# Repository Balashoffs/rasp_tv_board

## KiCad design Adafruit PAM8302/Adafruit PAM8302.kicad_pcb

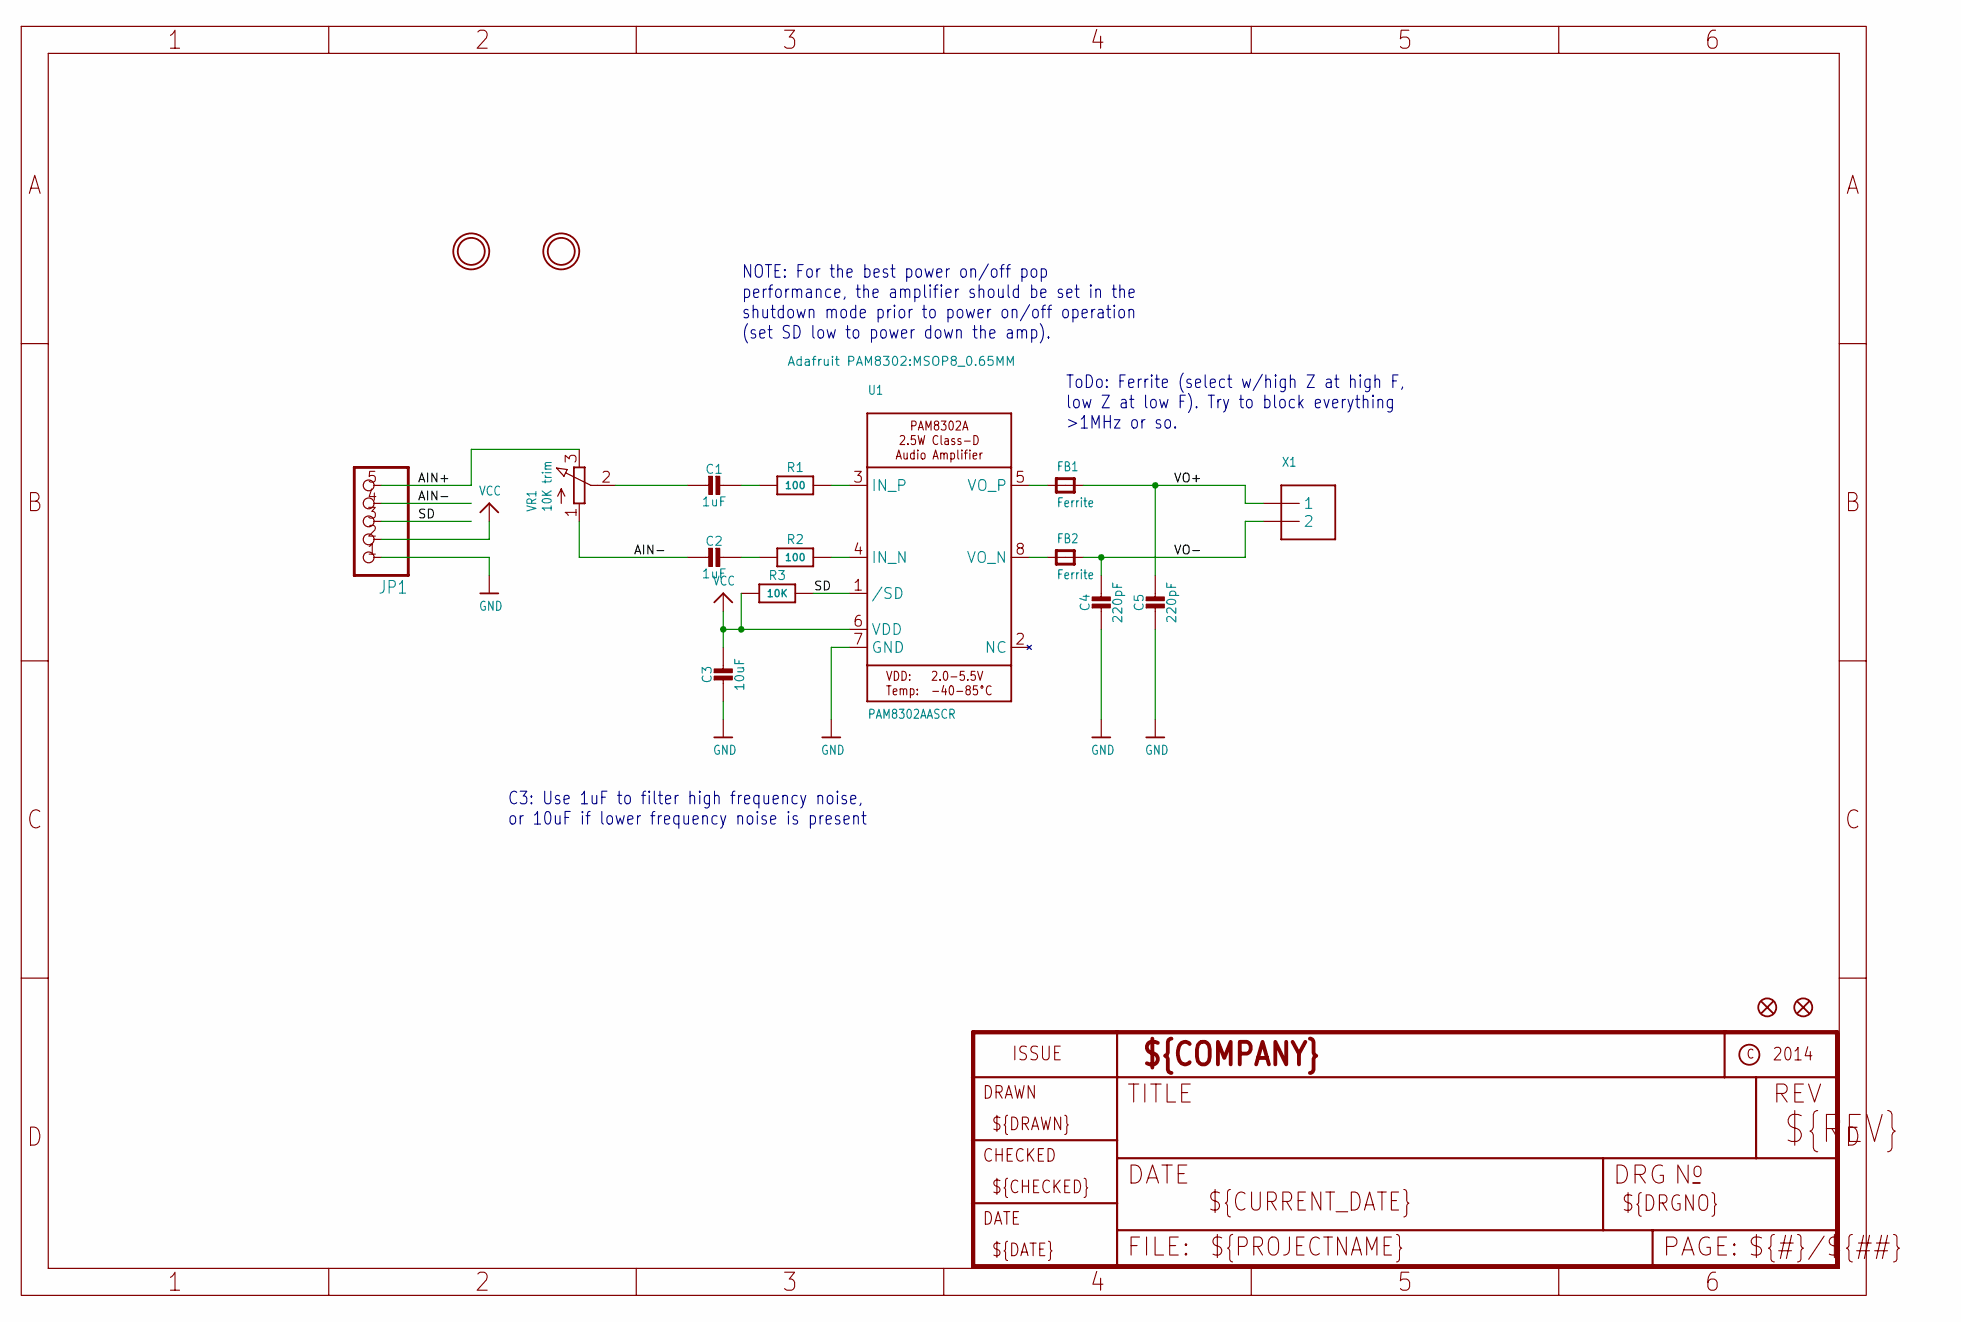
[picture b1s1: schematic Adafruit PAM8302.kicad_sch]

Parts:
C1, C2: 1uF; 0805-NO
C3: 10uF; 0805-NO
C4, C5: 220pF; 0805-NO
FB1, FB2: Ferrite; _0805
FID1, FID2: FIDUCIAL""; FIDUCIAL_1MM
JP1: HEADER-1X570MIL; 1X05_ROUND_70
R1, R2: 100; 0805-NO
R3: 10K; 0805-NO
U1: PAM8302AASCR; MSOP8_0.65MM
U$10, U$11: MOUNTINGHOLE2.0; MOUNTINGHOLE_2.0_PLATED
VR1: 10K trim; TRIMPOT_BOURNS_3303W
X1: TERMBLOCK_1X2; TERMBLOCK_1X2-3.5MM

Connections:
AIN+: JP1.5, VR1.3 (E)
AIN-: C2.2, JP1.4, VR1.1 (A)
GND: C3.2, C4.2, C5.2, JP1.1, U1.7 (GND)
unnamed: R2.2, U1.4 (IN_N)
unnamed: R1.2, U1.3 (IN_P)
unnamed: C1.1, R1.1
unnamed: C2.1, R2.1
unnamed: FB2.1, U1.8 (VO_N)
unnamed: FB1.1, U1.5 (VO_P)
unnamed: C1.2, VR1.2 (S)
SD: JP1.3, R3.2, U1.1 (/SD)
VCC: C3.1, JP1.2, R3.1, U1.6 (VDD)
VO+: C5.1, FB1.2, X1.1
VO-: C4.1, FB2.2, X1.2

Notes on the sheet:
ToDo: Ferrite (select w/high Z at high F, low Z at low F). Try to block everything >1MHz or so.
C3: Use 1uF to filter high frequency noise, or 10uF if lower frequency noise is present
NOTE: For the best power on/off pop performance, the amplifier should be set in the shutdown mode prior to power on/off operation (set SD low to power down the amp).

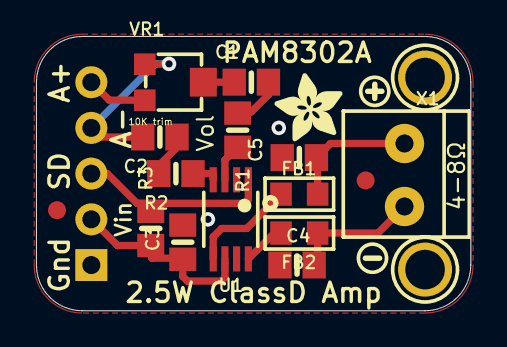
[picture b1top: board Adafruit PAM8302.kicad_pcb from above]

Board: 2 copper layers, 24.1 x 15.2 mm, 22 parts (1 on the bottom side), 14 nets.

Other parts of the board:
U$3: SYMBOL_PLUS
U$4: SYMBOL_MINUS
U$5: ADAFRUIT_3.5MM
U$6: PCBFEAT-REV-040

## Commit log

2025-12-05 init
2025-12-05 second commit
2025-12-05 add PAM
2025-12-07 make pcb routing
2025-12-07 finish board with 2.8 spi
2025-12-08 release 2.8
2025-12-14 ready for factory
2025-12-14 add picure of models
